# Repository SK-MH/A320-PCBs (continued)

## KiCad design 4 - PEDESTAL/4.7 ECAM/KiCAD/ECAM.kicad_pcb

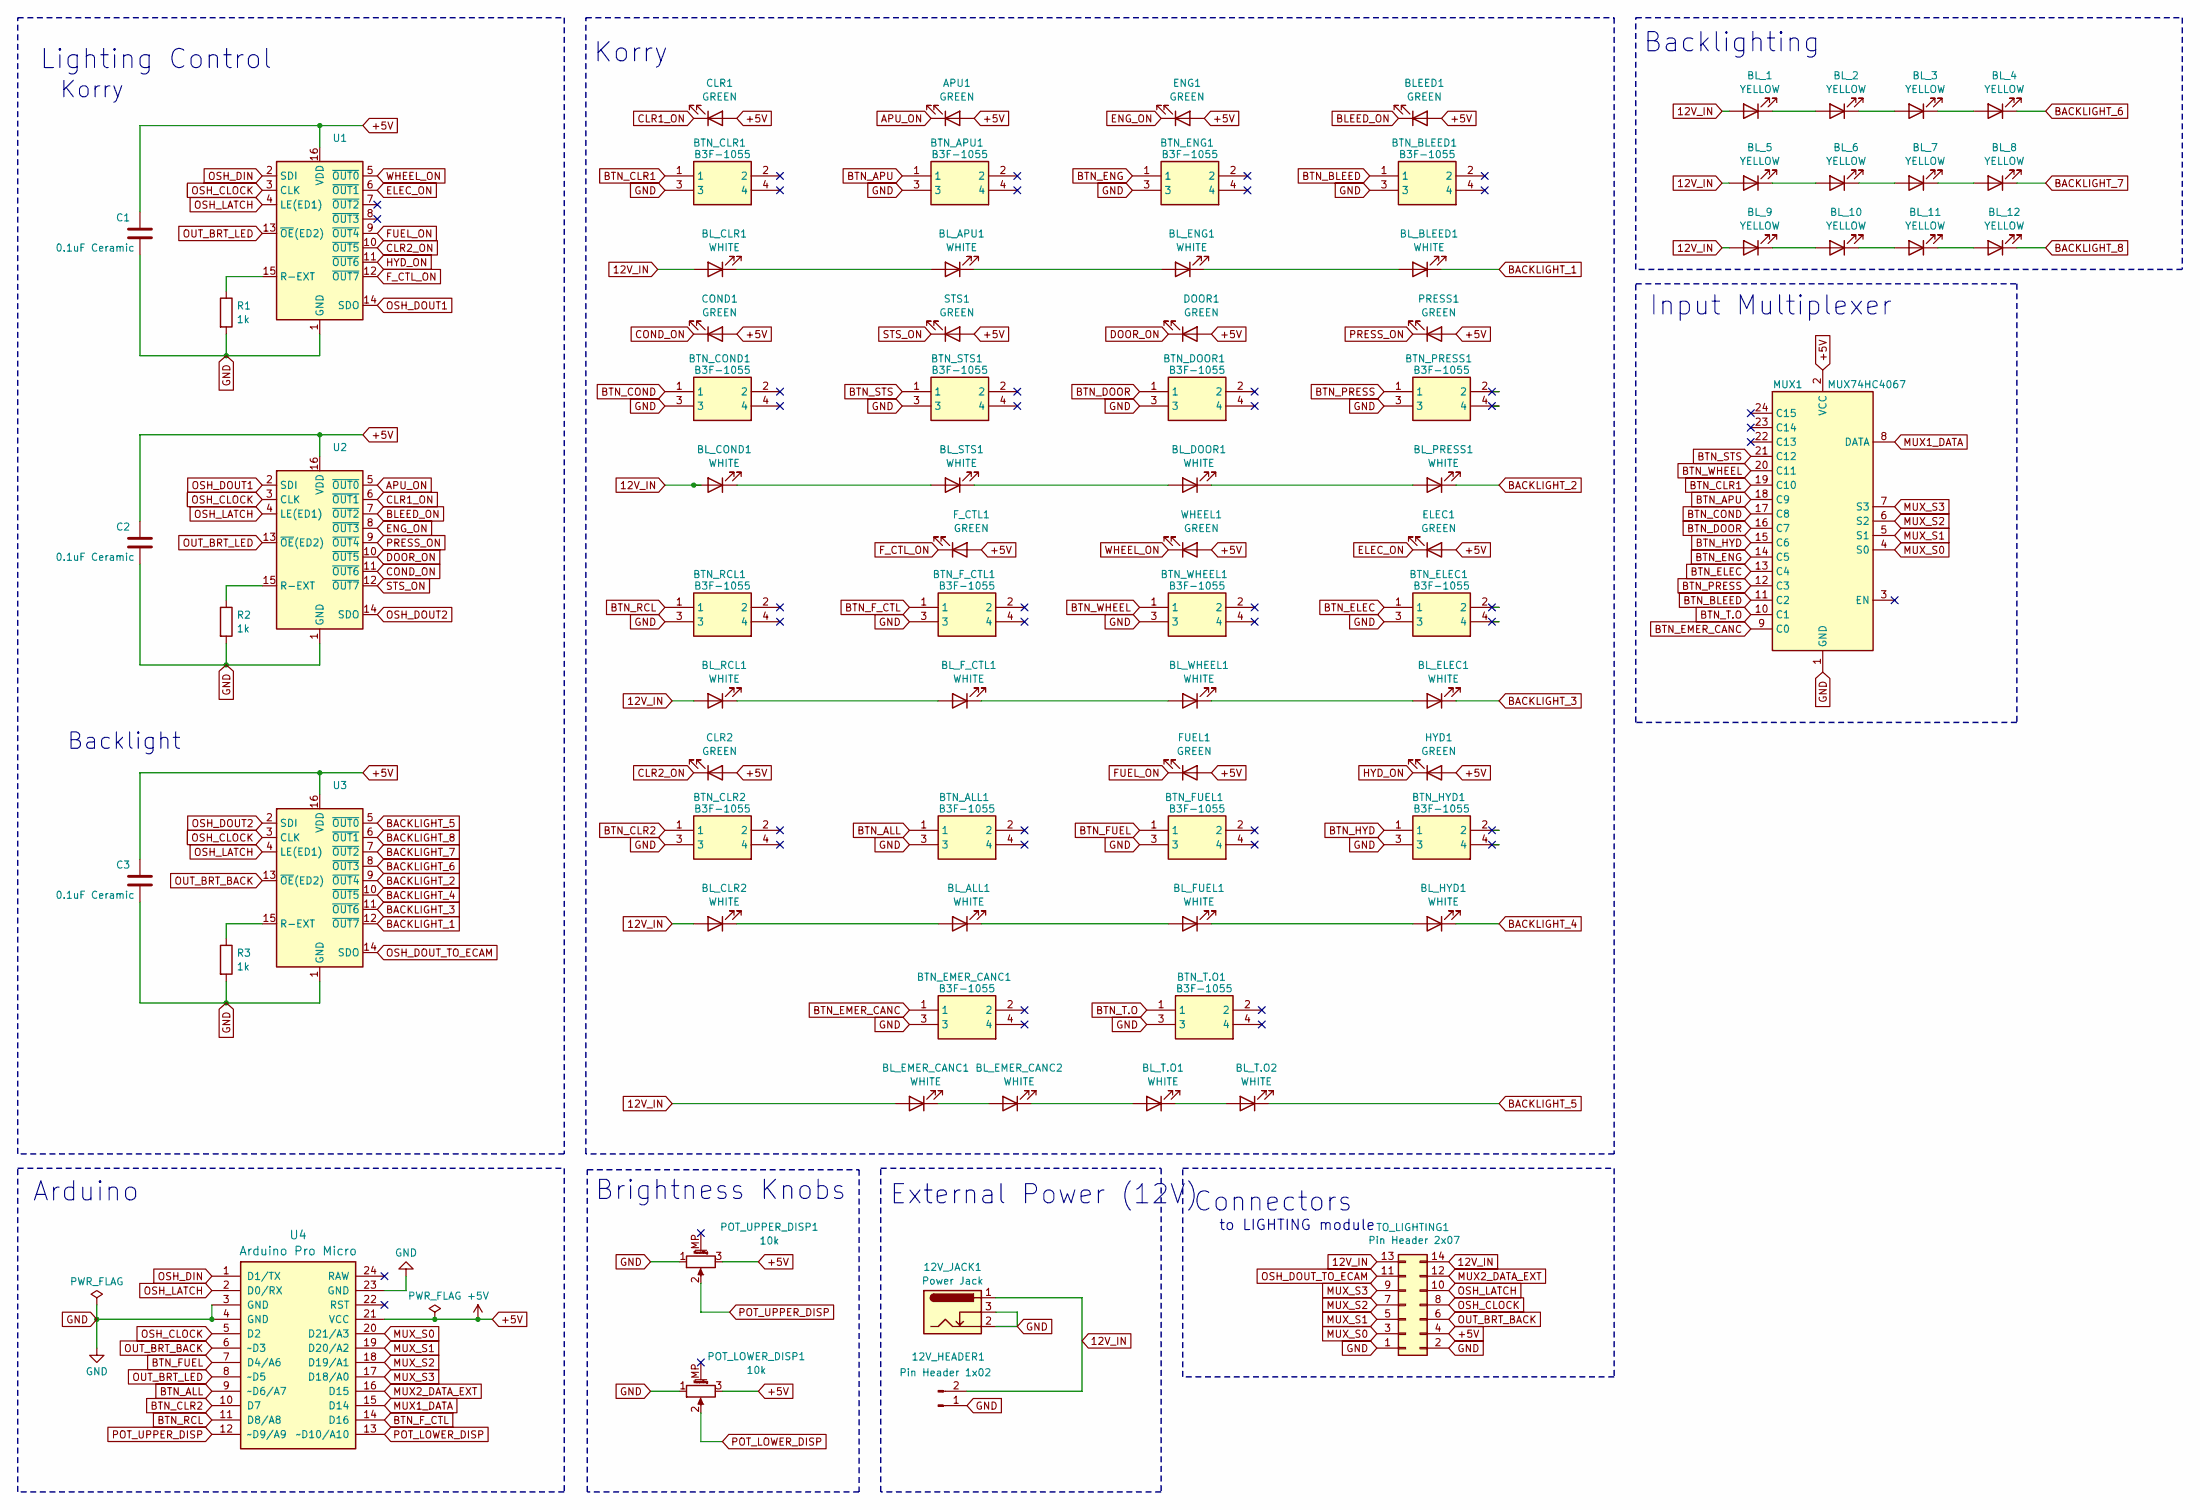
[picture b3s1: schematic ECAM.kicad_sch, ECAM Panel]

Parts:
12V_HEADER1: Pin Header 1x02; JST_EH_B2B-EH-A_1x02_P2.50mm_Vertical
12V_JACK1: Power Jack; BarrelJack_Horizontal
APU1: GREEN; LED_D3.0mm
BLEED1: GREEN; LED_D3.0mm
BL_1, BL_2, BL_3, BL_4, BL_5, BL_6, BL_7, BL_8, BL_9, BL_10, BL_11, BL_12: YELLOW; LED_D3.0mm
BL_ALL1: WHITE; LED_D3.0mm
BL_APU1: WHITE; LED_D3.0mm
BL_BLEED1: WHITE; LED_D3.0mm
BL_CLR1, BL_CLR2: WHITE; LED_D3.0mm
BL_COND1: WHITE; LED_D3.0mm
BL_DOOR1: WHITE; LED_D3.0mm
BL_ELEC1: WHITE; LED_D3.0mm
BL_EMER_CANC1, BL_EMER_CANC2: WHITE; LED_D3.0mm
BL_ENG1: WHITE; LED_D3.0mm
BL_FUEL1: WHITE; LED_D3.0mm
BL_F_CTL1: WHITE; LED_D3.0mm
BL_HYD1: WHITE; LED_D3.0mm
BL_PRESS1: WHITE; LED_D3.0mm
BL_RCL1: WHITE; LED_D3.0mm
BL_STS1: WHITE; LED_D3.0mm
BL_T.O1, BL_T.O2: WHITE; LED_D3.0mm
BL_WHEEL1: WHITE; LED_D3.0mm
BTN_ALL1: B3F-1055; B3F1000; Mouser Part Number 653-B3F-1055
BTN_APU1: B3F-1055; B3F1000; Mouser Part Number 653-B3F-1055
BTN_BLEED1: B3F-1055; B3F1000; Mouser Part Number 653-B3F-1055
BTN_CLR1, BTN_CLR2: B3F-1055; B3F1000; Mouser Part Number 653-B3F-1055
BTN_COND1: B3F-1055; B3F1000; Mouser Part Number 653-B3F-1055
BTN_DOOR1: B3F-1055; B3F1000; Mouser Part Number 653-B3F-1055
BTN_ELEC1: B3F-1055; B3F1000; Mouser Part Number 653-B3F-1055
BTN_EMER_CANC1: B3F-1055; B3F1000; Mouser Part Number 653-B3F-1055
BTN_ENG1: B3F-1055; B3F1000; Mouser Part Number 653-B3F-1055
BTN_FUEL1: B3F-1055; B3F1000; Mouser Part Number 653-B3F-1055
BTN_F_CTL1: B3F-1055; B3F1000; Mouser Part Number 653-B3F-1055
BTN_HYD1: B3F-1055; B3F1000; Mouser Part Number 653-B3F-1055
BTN_PRESS1: B3F-1055; B3F1000; Mouser Part Number 653-B3F-1055
BTN_RCL1: B3F-1055; B3F1000; Mouser Part Number 653-B3F-1055
BTN_STS1: B3F-1055; B3F1000; Mouser Part Number 653-B3F-1055
BTN_T.O1: B3F-1055; B3F1000; Mouser Part Number 653-B3F-1055
BTN_WHEEL1: B3F-1055; B3F1000; Mouser Part Number 653-B3F-1055
C1, C2, C3: 0.1uF Ceramic; C_Disc_D3.0mm_W1.6mm_P2.50mm
CLR1, CLR2: GREEN; LED_D3.0mm
COND1: GREEN; LED_D3.0mm
DOOR1: GREEN; LED_D3.0mm
ELEC1: GREEN; LED_D3.0mm
ENG1: GREEN; LED_D3.0mm
FUEL1: GREEN; LED_D3.0mm
F_CTL1: GREEN; LED_D3.0mm
HYD1: GREEN; LED_D3.0mm
MUX1: MUX74HC4067
POT_LOWER_DISP1: 10k; Potentiometer_Alps_RK09K_Single_Vertical
POT_UPPER_DISP1: 10k; Potentiometer_Alps_RK09K_Single_Vertical
PRESS1: GREEN; LED_D3.0mm
R1, R2, R3: 1k; R_Axial_DIN0204_L3.6mm_D1.6mm_P5.08mm_Horizontal
STS1: GREEN; LED_D3.0mm
TO_LIGHTING1: Pin Header 2x07; IDC-Header_2x07_P2.54mm_Vertical
U1, U2, U3: TLC5917; DIP-16_W7.62mm
U4: Arduino Pro Micro; Sparkfun_Pro_Micro
WHEEL1: GREEN; LED_D3.0mm

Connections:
12V_IN: 12V_HEADER1.2, 12V_JACK1.1, BL_1.2 (A), BL_5.2 (A), BL_9.2 (A), BL_CLR1.2 (A), BL_CLR2.2 (A), BL_COND1.2 (A), BL_EMER_CANC1.2 (A), BL_RCL1.2 (A), TO_LIGHTING1.13, TO_LIGHTING1.14
+5V: APU1.2 (A), BLEED1.2 (A), C1.1, C2.1, C3.1, CLR1.2 (A), CLR2.2 (A), COND1.2 (A), DOOR1.2 (A), ELEC1.2 (A), ENG1.2 (A), FUEL1.2 (A), F_CTL1.2 (A), HYD1.2 (A), MUX1.2 (VCC), POT_LOWER_DISP1.3, POT_UPPER_DISP1.3, PRESS1.2 (A), STS1.2 (A), TO_LIGHTING1.4, U1.16 (VDD), U2.16 (VDD), U3.16 (VDD), U4.21 (VCC), WHEEL1.2 (A)
APU_ON: APU1.1 (K), U2.5 (~OUT0)
BACKLIGHT_1: BL_BLEED1.1 (K), U3.12 (~OUT7)
BACKLIGHT_2: BL_PRESS1.1 (K), U3.9 (~OUT4)
BACKLIGHT_3: BL_ELEC1.1 (K), U3.11 (~OUT6)
BACKLIGHT_4: BL_HYD1.1 (K), U3.10 (~OUT5)
BACKLIGHT_5: BL_T.O2.1 (K), U3.5 (~OUT0)
BACKLIGHT_6: BL_4.1 (K), U3.8 (~OUT3)
BACKLIGHT_7: BL_8.1 (K), U3.7 (~OUT2)
BACKLIGHT_8: BL_12.1 (K), U3.6 (~OUT1)
BLEED_ON: BLEED1.1 (K), U2.7 (~OUT2)
BTN_ALL: BTN_ALL1.1, U4.9 (~D6/A7)
BTN_APU: BTN_APU1.1, MUX1.18 (C9)
BTN_BLEED: BTN_BLEED1.1, MUX1.11 (C2)
BTN_CLR1: BTN_CLR1.1, MUX1.19 (C10)
BTN_CLR2: BTN_CLR2.1, U4.10 (D7)
BTN_COND: BTN_COND1.1, MUX1.17 (C8)
BTN_DOOR: BTN_DOOR1.1, MUX1.16 (C7)
BTN_ELEC: BTN_ELEC1.1, MUX1.13 (C4)
BTN_EMER_CANC: BTN_EMER_CANC1.1, MUX1.9 (C0)
BTN_ENG: BTN_ENG1.1, MUX1.14 (C5)
BTN_FUEL: BTN_FUEL1.1, U4.7 (D4/A6)
BTN_F_CTL: BTN_F_CTL1.1, U4.14 (D16)
BTN_HYD: BTN_HYD1.1, MUX1.15 (C6)
BTN_PRESS: BTN_PRESS1.1, MUX1.12 (C3)
BTN_RCL: BTN_RCL1.1, U4.11 (D8/A8)
BTN_STS: BTN_STS1.1, MUX1.21 (C12)
BTN_T.O: BTN_T.O1.1, MUX1.10 (C1)
BTN_WHEEL: BTN_WHEEL1.1, MUX1.20 (C11)
CLR1_ON: CLR1.1 (K), U2.6 (~OUT1)
CLR2_ON: CLR2.1 (K), U1.10 (~OUT5)
COND_ON: COND1.1 (K), U2.11 (~OUT6)
DOOR_ON: DOOR1.1 (K), U2.10 (~OUT5)
ELEC_ON: ELEC1.1 (K), U1.6 (~OUT1)
ENG_ON: ENG1.1 (K), U2.8 (~OUT3)
FUEL_ON: FUEL1.1 (K), U1.9 (~OUT4)
F_CTL_ON: F_CTL1.1 (K), U1.12 (~OUT7)
GND: 12V_HEADER1.1, 12V_JACK1.2, 12V_JACK1.3, BTN_ALL1.3, BTN_APU1.3, BTN_BLEED1.3, BTN_CLR1.3, BTN_CLR2.3, BTN_COND1.3, BTN_DOOR1.3, BTN_ELEC1.3, BTN_EMER_CANC1.3, BTN_ENG1.3, BTN_FUEL1.3, BTN_F_CTL1.3, BTN_HYD1.3, BTN_PRESS1.3, BTN_RCL1.3, BTN_STS1.3, BTN_T.O1.3, BTN_WHEEL1.3, C1.2, C2.2, C3.2, MUX1.1 (GND), POT_LOWER_DISP1.1, POT_UPPER_DISP1.1, R1.2, R2.2, R3.2, TO_LIGHTING1.1, TO_LIGHTING1.2, U1.1 (GND), U2.1 (GND), U3.1 (GND), U4.3 (GND), U4.4 (GND), U4.23 (GND)
HYD_ON: HYD1.1 (K), U1.11 (~OUT6)
MUX1_DATA: MUX1.8 (DATA), U4.15 (D14)
MUX2_DATA_EXT: TO_LIGHTING1.12, U4.16 (D15)
MUX_S0: MUX1.4 (S0), TO_LIGHTING1.3, U4.20 (D21/A3)
MUX_S1: MUX1.5 (S1), TO_LIGHTING1.5, U4.19 (D20/A2)
MUX_S2: MUX1.6 (S2), TO_LIGHTING1.7, U4.18 (D19/A1)
MUX_S3: MUX1.7 (S3), TO_LIGHTING1.9, U4.17 (D18/A0)
unnamed: BL_1.1 (K), BL_2.2 (A)
unnamed: BL_2.1 (K), BL_3.2 (A)
unnamed: BL_3.1 (K), BL_4.2 (A)
unnamed: BL_5.1 (K), BL_6.2 (A)
unnamed: BL_6.1 (K), BL_7.2 (A)
unnamed: BL_7.1 (K), BL_8.2 (A)
unnamed: BL_9.1 (K), BL_10.2 (A)
unnamed: BL_10.1 (K), BL_11.2 (A)
unnamed: BL_11.1 (K), BL_12.2 (A)
unnamed: BL_ALL1.2 (A), BL_CLR2.1 (K)
unnamed: BL_ALL1.1 (K), BL_FUEL1.2 (A)
unnamed: BL_APU1.2 (A), BL_CLR1.1 (K)
unnamed: BL_APU1.1 (K), BL_ENG1.2 (A)
unnamed: BL_BLEED1.2 (A), BL_ENG1.1 (K)
unnamed: BL_COND1.1 (K), BL_STS1.2 (A)
unnamed: BL_DOOR1.2 (A), BL_STS1.1 (K)
unnamed: BL_DOOR1.1 (K), BL_PRESS1.2 (A)
unnamed: BL_ELEC1.2 (A), BL_WHEEL1.1 (K)
unnamed: BL_EMER_CANC1.1 (K), BL_EMER_CANC2.2 (A)
unnamed: BL_EMER_CANC2.1 (K), BL_T.O1.2 (A)
unnamed: BL_FUEL1.1 (K), BL_HYD1.2 (A)
unnamed: BL_F_CTL1.2 (A), BL_RCL1.1 (K)
unnamed: BL_F_CTL1.1 (K), BL_WHEEL1.2 (A)
unnamed: BL_T.O1.1 (K), BL_T.O2.2 (A)
unnamed: R1.1, U1.15 (R-EXT)
unnamed: R2.1, U2.15 (R-EXT)
unnamed: R3.1, U3.15 (R-EXT)
OSH_CLOCK: TO_LIGHTING1.8, U1.3 (CLK), U2.3 (CLK), U3.3 (CLK), U4.5 (D2)
OSH_DIN: U1.2 (SDI), U4.1 (D1/TX)
OSH_DOUT1: U1.14 (SDO), U2.2 (SDI)
OSH_DOUT2: U2.14 (SDO), U3.2 (SDI)
OSH_DOUT_TO_ECAM: TO_LIGHTING1.11, U3.14 (SDO)
OSH_LATCH: TO_LIGHTING1.10, U1.4 (LE(ED1)), U2.4 (LE(ED1)), U3.4 (LE(ED1)), U4.2 (D0/RX)
OUT_BRT_BACK: TO_LIGHTING1.6, U3.13 (~OE(ED2)), U4.6 (~D3)
OUT_BRT_LED: U1.13 (~OE(ED2)), U2.13 (~OE(ED2)), U4.8 (~D5)
POT_LOWER_DISP: POT_LOWER_DISP1.2, U4.13 (~D10/A10)
POT_UPPER_DISP: POT_UPPER_DISP1.2, U4.12 (~D9/A9)
PRESS_ON: PRESS1.1 (K), U2.9 (~OUT4)
STS_ON: STS1.1 (K), U2.12 (~OUT7)
WHEEL_ON: U1.5 (~OUT0), WHEEL1.1 (K)

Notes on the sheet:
Connectors
Korry
Arduino
Backlight
Backlighting
Brightness Knobs
External Power (12V)
Lighting Control
Input Multiplexer
to LIGHTING module

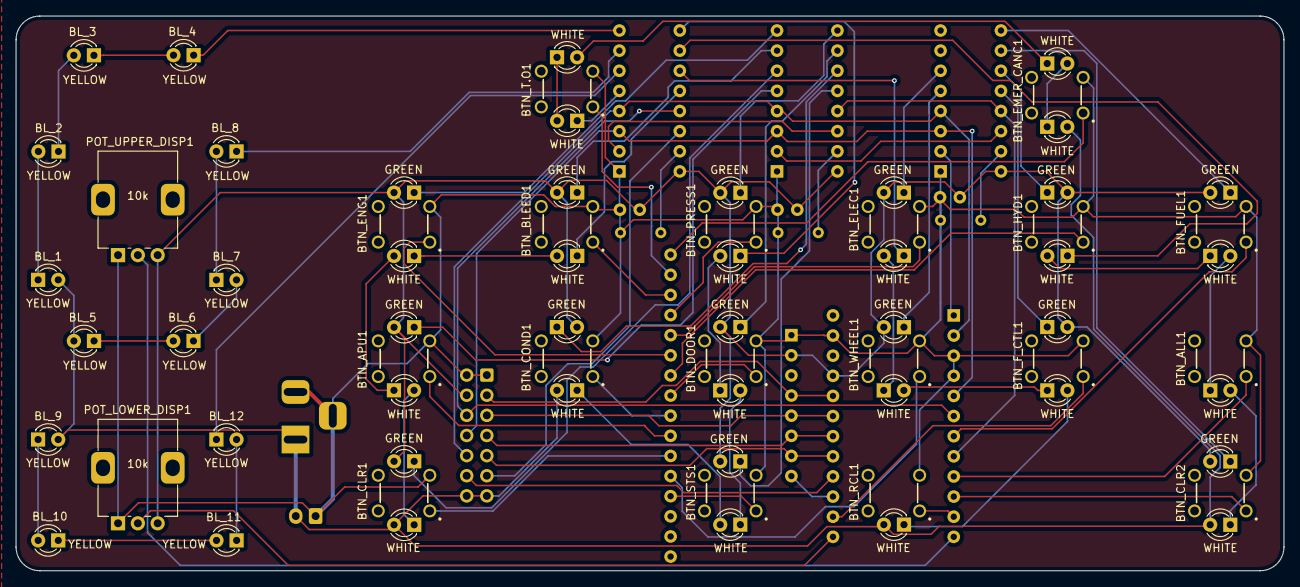
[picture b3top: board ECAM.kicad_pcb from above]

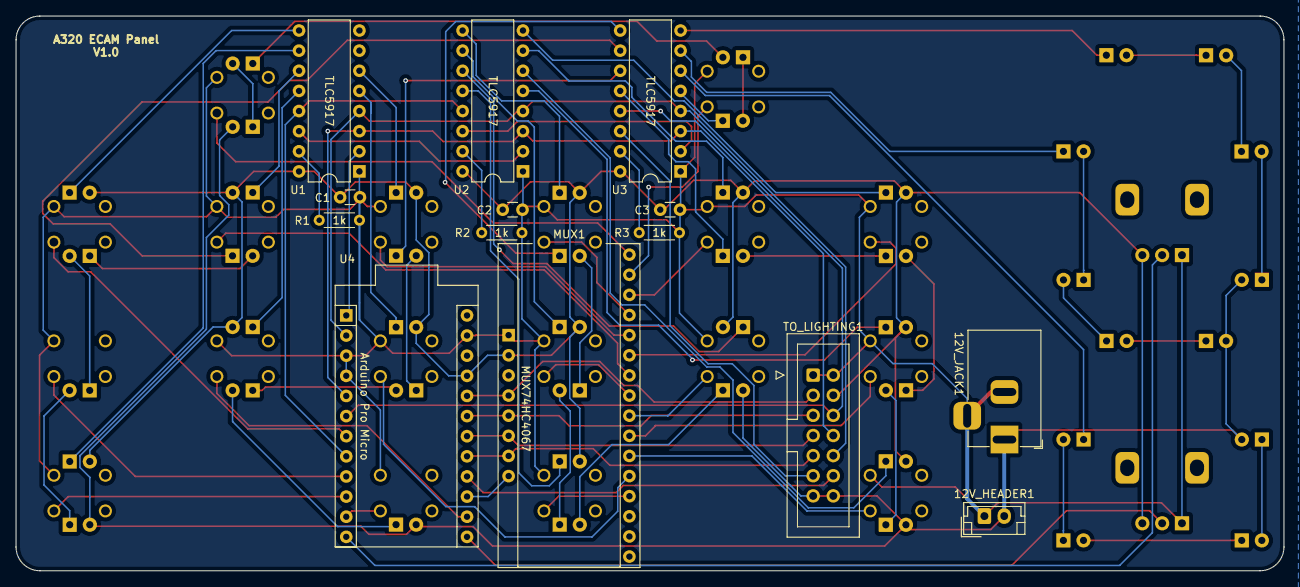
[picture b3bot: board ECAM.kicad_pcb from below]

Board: 2 copper layers, 160.0 x 70.0 mm, 80 parts (14 on the bottom side), 86 nets.
